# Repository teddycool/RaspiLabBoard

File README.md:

# RaspiLabBoard
A circuit board and a python lib to make it easier to demonstarte and try things out on a RasberryPi. The board was made to try out AWS greengrass with a raspberry pi as a device with CAN capabillities but can of course be used for other purposes as well. 

The board is a raspberry pi hat that fits in to the IO.

The circuit-board, ordererd from aisler.net, see: https://aisler.net/p/SKYVGCNC 

Assembled circuitboard with a pi in the background. Ready to use :-)

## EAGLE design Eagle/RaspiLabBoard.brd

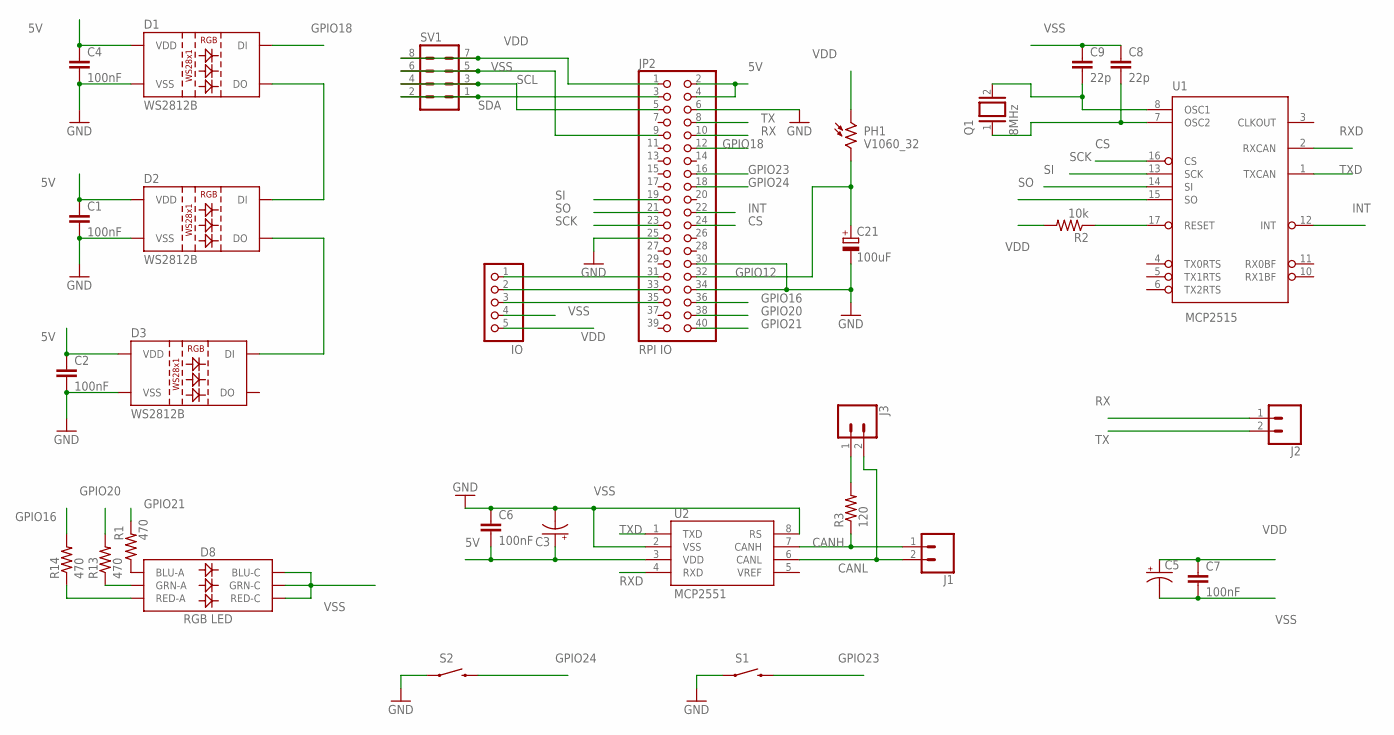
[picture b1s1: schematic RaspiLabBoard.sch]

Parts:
C1, C2, C4, C6, C7: 100nF; 0805
C3, C5: CPOL-USE2-5; E2-5
C8, C9: 22p; 0805
C21: 100uF; E5-10,5
D1, D2, D3: WS2812B
D8: RGB LED; LED-TRICOLOR-5050
J1, J2, J3: CONN_02; 1X02
JP2: RPI IO; 2X20
JP4: IO; 1X05
PH1: V1060_32; TO-5_V10
Q1: 8MHz; QS
R1, R13, R14: 470; 0805
R2: 10k; 0805
R3: 120; 0805
S1, S2: RESET; TACTILE-SWITCH-1101NE
SV1: MA04-2
U1: MCP2515; SO18W
U2: MCP2551; SO08

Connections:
5V: C1.1, C2.1, C3.+, C4.1, C6.2, D1.1 (VDD), D2.1 (VDD), D3.1 (VDD), JP2.2, JP2.4, U2.3 (VDD)
CANH: J1.1, R3.1, U2.7 (CANH)
CANL: J1.2, J3.2, U2.6 (CANL)
CS: JP2.24, U1.16 (CS)
GPIO6: JP2.31, JP4.1
GPIO12: C21.+, JP2.32, PH1.2
GPIO13: JP2.33, JP4.2
GPIO16: JP2.36, R14.2
GPIO18: D1.4 (DI), JP2.12
GPIO19: JP2.35, JP4.3
GPIO20: JP2.38, R13.2
GPIO21: JP2.40, R1.2
GPIO23: JP2.16, S1.2
GPIO24: JP2.18, S2.2
INT: JP2.22, U1.12 (INT)
unnamed: D2.2 (DO), D3.4 (DI)
unnamed: D8.1 (GRN-A), R13.1
unnamed: D8.3 (BLU-A), R1.1
unnamed: R2.1, U1.17 (RESET)
unnamed: C9.2, Q1.2, U1.8 (OSC1)
unnamed: D8.2 (RED-A), R14.1
unnamed: C8.2, Q1.1, U1.7 (OSC2)
unnamed: J3.1, R3.2
unnamed: D1.2 (DO), D2.4 (DI)
RX: J2.1, JP2.10
RXD: U1.2 (RXCAN), U2.4 (RXD)
SCK: JP2.23, U1.13 (SCK)
SCL: JP2.5, SV1.3, SV1.4
SDA: JP2.3, SV1.1, SV1.2
SI: JP2.19, U1.14 (SI)
SO: JP2.21, U1.15 (SO)
TX: J2.2, JP2.8
TXD: U1.1 (TXCAN), U2.1 (TXD)
VDD: C5.+, C7.1, JP2.1, JP4.5, PH1.1, R2.2, SV1.7, SV1.8, U1.18 (VDD)
VSS: C1.2, C2.2, C3.-, C4.2, C5.-, C6.1, C7.2, C8.1, C9.1, C21.-, D1.3 (VSS), D2.3 (VSS), D3.3 (VSS), D8.4 (BLU-C), D8.5 (RED-C), D8.6 (GRN-C), JP2.6, JP2.9, JP2.25, JP2.30, JP2.34, JP4.4, S1.1, S2.1, SV1.5, SV1.6, U1.9 (VSS), U2.2 (VSS), U2.8 (RS)

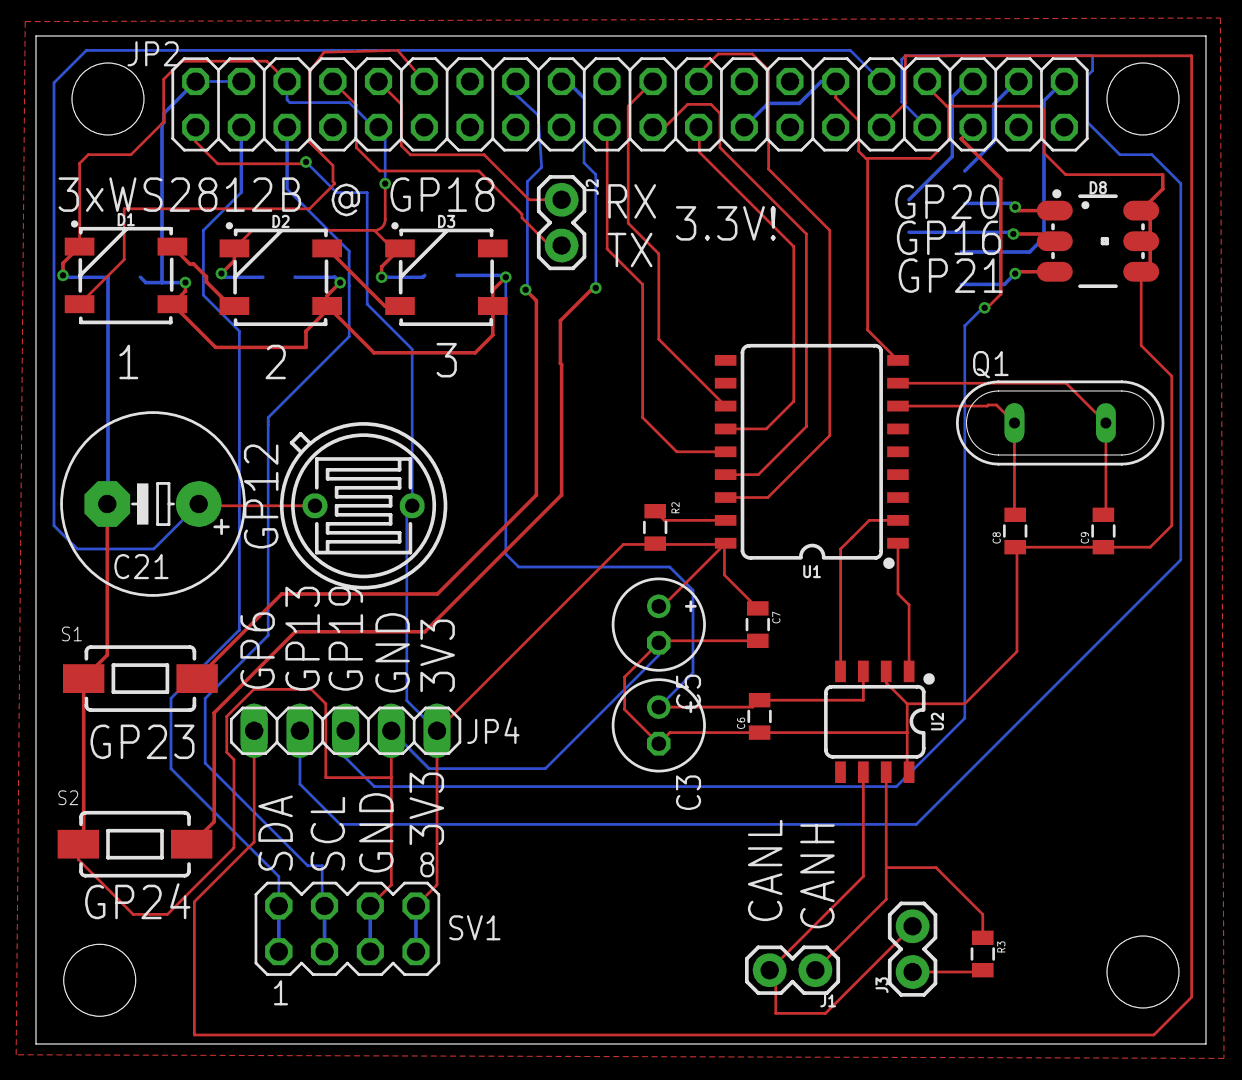
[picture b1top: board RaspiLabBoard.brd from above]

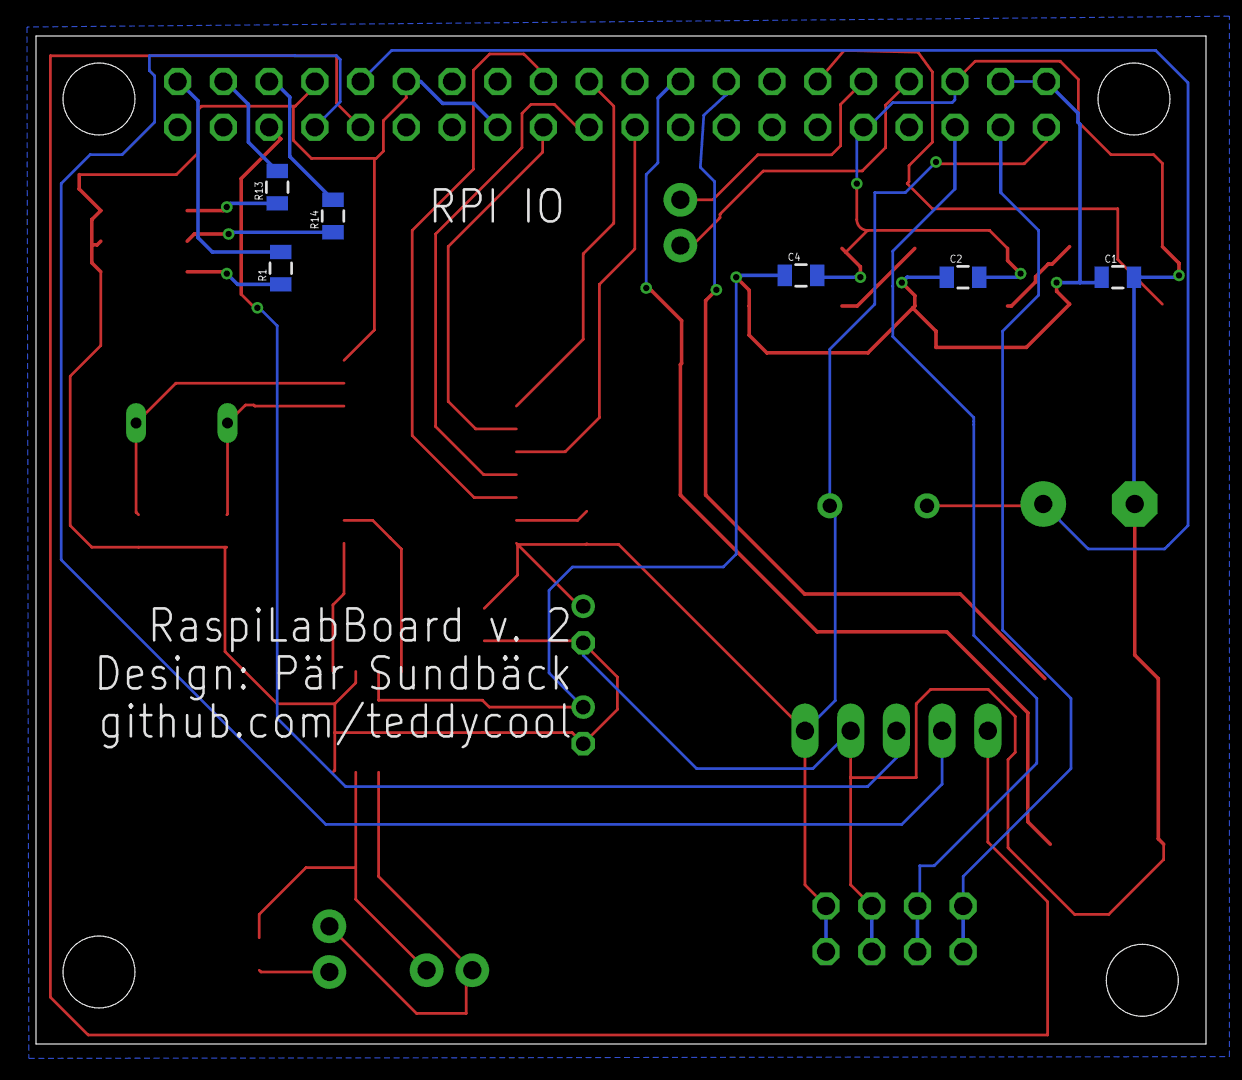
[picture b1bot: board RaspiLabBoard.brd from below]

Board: 2 copper layers, 65.0 x 56.0 mm, 31 parts (6 on the bottom side), 35 nets.

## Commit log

2019-03-14 First commit
    First commit of this repo. The hardware and first version of test-code in python
2019-03-14 Some pictures
2019-03-14 Pictures
2019-03-14 deleted some files
2019-03-22 Started working with sw for hw version 2
2019-05-09 CAN test added
2019-05-10 test
2019-05-19 Hardware version 2
    As ordered from Aisler.net 20190519
2019-05-19 fixing pdf and history
2019-05-19 Fixing documents...

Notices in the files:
parts and their libraries:
SparkFun-LED: Licensing: Creative Commons ShareAlike 4.0 International - https://creativecommons.org/licenses/by-sa/4.0
